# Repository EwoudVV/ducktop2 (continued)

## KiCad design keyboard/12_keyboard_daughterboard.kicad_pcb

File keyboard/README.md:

# keyboard

the RGB map now follows the physical rows. the board is four layers and
0.8 mm thick, with the same 273.5 x 80 mm outline, 65 key positions, diodes
and J320 position. the existing switch, power and I2C routing is retained.
the local joins between each LED's three anodes are retained too. old links
between incompatible LED banks were cleared or trimmed for the new map.

switches, LEDs and the cable connector stay in their original locked positions.
this is still a routing revision, not an order release.

open `12_keyboard_daughterboard.kicad_pro` in this folder. the schematic,
PCB, rules and library tables beside it are the current files.

the layer plan is F.Cu for components and signals, In1.Cu for GND,
In2.Cu for extra signals and local power copper, and B.Cu for signals and
ground fill. a rule blocks non-ground tracks on In1.Cu while allowing
signal vias through it. the current ground zone and stitching are retained.
the dielectric build is provisional; confirm a 0.8 mm four-layer stackup
with the fabricator before ordering.

## LEDs and power

i picked Everlight `19-337/R6GHBHC-C02/2T` LEDs, LCSC `C409504`. each is
1.6 x 1.6 x 0.35 mm and has separate connections for all three colours.
the IS31FL3743A driver, U320, handles all 65 keys over I2C at address
`0x2f`. there is no daisy-chained data connection between the LEDs.

each LED sits 2.8 mm above its switch centre in the top view, inside
CHERRY's auxiliary component area. the maximum LED body height is
0.45 mm; allowing 0.05 mm of solder gives 0.50 mm against CHERRY's
0.8 mm limit. the copper pads fit the allowed area too, with a minimum
nominal edge margin of 0.075 mm. check the first assembled LED and switch
before fitting the rest. the LEDs have to go on before the switches.

R320 is 33.2k, 1%. using the driver's published maximum current at its
stated 3.6 V / 25 C test condition and the resistor's low tolerance gives
11.23 mA per active sink. only 18 sinks run at once, so the total is about
0.202 A before logic and pull-ups. the 5 V feed has a 0.25 A design budget,
below U310's roughly 0.4 A nominal limit and J320's 0.5 A contact rating.
this is a design calculation; measure current and driver temperature at
full white on the first assembled board. the scan duty also means the
average current per colour is about 1 mA at full brightness.

the keyboard gets switched 5 V on J320 pin 29. its 3.3 V buffer supply is
pin 2, through the now-populated R387 on the center board. **keep R386
unpopulated**, since it bypasses the current-limited switch. U321 is a
TCA9517A: its A side faces the main 3.3 V bus and its B side faces the 5 V
RGB driver. this keeps the
unpowered driver isolated. do not swap its sides or put 5 V pull-ups on
the EC side.

## routing order

1. start with U320's exposed ground pad, supply pins and decoupling.
   keep C322/C323 close to VCC, C324/C325 close to PVCC, and C320 beside
   U321's 3.3 V pin. give the exposed pad a short, broad ground connection
   and a return to the In1.Cu ground plane. keep ordinary open vias out of
   the exposed paste area; agree any filled or capped thermal vias with
   the assembler. R320 should have a quiet return to U320's ground.
2. route the 5 V feed and ground returns with at least the selected
   0.5 mm width where space allows. use short neckdowns at fine-pitch pads.
   add the In1.Cu ground plane, ground fill on the outer layers and enough
   stitching to connect the surface pads. preserve the switch keepouts.
3. route the RGB scan banks mainly down the keyboard and the colour sinks
   along the key rows. each bank has one key from every physical row, with
   one extra key on ten banks. use the table below and the [key map](rgb-key-map.csv).
   RGB_SW feeds use 0.4 mm and sinks use 0.2 mm. local anode joins already
   belong to their new bank; do not join neighbouring LEDs just because
   they used to share a bank.
4. finish any remaining keyboard-matrix and I2C connections at 0.2 mm. there is no controlled
   impedance requirement here. keep I2C away from long parallel LED power
   runs, and keep the driver-side pull-ups local. do not add extra EC-side
   pull-ups. the matrix diode direction is already set in the schematic.
5. add ground stitching, refill, and run DRC with schematic parity.
   check the full native unconnected count: the CLI report stops at 499.
   the current saved routing count is recorded in the [checks](../verification/keyboard-rgb.md).

| physical row | red cathode | green cathode | blue cathode |
| --- | --- | --- | --- |
| number row | RGB_RED01 | RGB_CS02 | RGB_CS03 |
| Q row | RGB_RED04 | RGB_CS05 | RGB_CS06 |
| home row | RGB_RED07 | RGB_CS08 | RGB_CS09 |
| shift row | RGB_RED10 | RGB_CS11 | RGB_CS12 |
| bottom row | RGB_RED13 | RGB_CS14 | RGB_CS15 |
| ten extra keys | RGB_RED16 | RGB_CS17 | RGB_CS18 |

55 keys use their physical row's sink group. the ten extra keys use the
last group, so two keys never share the same bank and colour channel.
R330-R335 remain between the driver's red CS outputs and the RGB_RED nets.
the firmware table and CSV use the same assignments as the schematic.

the minimum clearance and track width are 0.15 mm, with 0.5/0.2 mm vias.
these are routing settings, not a factory approval. confirm the final
0.8 mm stackup and manufacturing limits when ordering.

the 65 CHERRY copper-free rectangles are conservatively extended through
**all four layers**. do not put tracks, vias, pads or pours in them.
the custom courtyard rules allow
only each LED to sit under its matching switch. every other courtyard
check stays active. those exceptions depend on the checked LED offset
and body height, so leave the locked LED positions alone.

## firmware and checks

the EC now initialises the driver, loads all channels before enabling
light, and cuts RGB power on an I2C failure or the power-switch fault
signal. the existing host enable command turns on white at 64/255
brightness. per-key RGB and brightness functions are available in the
firmware; a desktop colour picker and animation controls are still to do.
updates happen one bank per main-loop call, so this is a static backlight
driver, not a high-frame-rate effects engine.

the [placement checks](../verification/keyboard-rgb.md) record the current
results. this revision has no fabrication package yet. after routing,
recheck the switch exclusions against the actual exported copper, then
prepare a new BOM, placement file and assembly sequence for the LEDs,
support parts and switches. the old passive-keyboard exporter refuses
this revision until its assembly contract is updated.

part drawings used here: [Everlight LED](https://www.endrich.com/Datenbl%C3%A4tter/Lichtl%C3%B6sungen/Everlight/RGB%20LED/19-337R6GHBHC-C022T.pdf),
[Lumissil driver](https://www.lumissil.com/assets/pdf/core/IS31FL3743A_DS.pdf),
[TI buffer](https://www.ti.com/lit/ds/symlink/tca9517a.pdf), and CHERRY's
VS-10107 revision 03 / PCB-MX-ULP sample drawings.

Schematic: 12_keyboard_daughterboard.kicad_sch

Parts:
C320: 100n 50V buffer 3V3; C_0603_1608Metric; MPN CL10B104KB8NNNC
C321: 10u 25V RGB input bulk; C_0805_2012Metric; MPN CL21A106KAYNNNE
C322: 1u 25V RGB VCC; C_0603_1608Metric; MPN CL10B105KA8NNNC
C323: 100n 50V RGB VCC; C_0603_1608Metric; MPN CL10B104KB8NNNC
C324: 1u 25V RGB PVCC; C_0603_1608Metric; MPN CL10B105KA8NNNC
C325: 100n 50V RGB PVCC / buffer B; C_0603_1608Metric; MPN CL10B104KB8NNNC
C326: 100n 50V RGB startup delay; C_0603_1608Metric; MPN CL10B104KB8NNNC
D320, D321, D322, D323, D324, D325, D326, D327, D328, D329, D330, D331, D332, D333, D334, D335, D336, D337, D338, D339, D340, D341, D342, D343, D344, D345, D346, D347, D348, D349, D350, D351, D352, D353, D354, D355, D356, D357, D358, D359, D360, D361, D362, D363, D364, D365, D366, D367, D368, D369, D370, D371, D372, D373, D374, D375, D376, D377, D378, D379, D380, D381, D382, D383, D384: 1N4148WS; D_SOD-323_JSCJ_1N4148WS; MPN 1N4148WS; LCSC C2128
J320: Keyboard FFC: MX ULP 5x14 matrix on 30-pin EC con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; Hirose_FH12_30_Separate_Mounts; MPN FH12-30S-0.5SH(55); LCSC C506793
LED320: RGB ESC; LED_Everlight_19-337_1616; MPN 19-337/R6GHBHC-C02/2T; LCSC C409504
LED321: RGB 1; LED_Everlight_19-337_1616; MPN 19-337/R6GHBHC-C02/2T; LCSC C409504
LED322: RGB 2; LED_Everlight_19-337_1616; MPN 19-337/R6GHBHC-C02/2T; LCSC C409504
LED323: RGB 3; LED_Everlight_19-337_1616; MPN 19-337/R6GHBHC-C02/2T; LCSC C409504
LED324: RGB 4; LED_Everlight_19-337_1616; MPN 19-337/R6GHBHC-C02/2T; LCSC C409504
LED325: RGB 5; LED_Everlight_19-337_1616; MPN 19-337/R6GHBHC-C02/2T; LCSC C409504
LED326: RGB 6; LED_Everlight_19-337_1616; MPN 19-337/R6GHBHC-C02/2T; LCSC C409504
LED327: RGB 7; LED_Everlight_19-337_1616; MPN 19-337/R6GHBHC-C02/2T; LCSC C409504
LED328: RGB 8; LED_Everlight_19-337_1616; MPN 19-337/R6GHBHC-C02/2T; LCSC C409504
LED329: RGB 9; LED_Everlight_19-337_1616; MPN 19-337/R6GHBHC-C02/2T; LCSC C409504
LED330: RGB 0; LED_Everlight_19-337_1616; MPN 19-337/R6GHBHC-C02/2T; LCSC C409504
LED331: RGB MINUS; LED_Everlight_19-337_1616; MPN 19-337/R6GHBHC-C02/2T; LCSC C409504
LED332: RGB EQUAL; LED_Everlight_19-337_1616; MPN 19-337/R6GHBHC-C02/2T; LCSC C409504
LED333: RGB BKSP; LED_Everlight_19-337_1616; MPN 19-337/R6GHBHC-C02/2T; LCSC C409504
LED334: RGB TAB; LED_Everlight_19-337_1616; MPN 19-337/R6GHBHC-C02/2T; LCSC C409504
LED335: RGB Q; LED_Everlight_19-337_1616; MPN 19-337/R6GHBHC-C02/2T; LCSC C409504
LED336: RGB W; LED_Everlight_19-337_1616; MPN 19-337/R6GHBHC-C02/2T; LCSC C409504
LED337: RGB E; LED_Everlight_19-337_1616; MPN 19-337/R6GHBHC-C02/2T; LCSC C409504
LED338: RGB R; LED_Everlight_19-337_1616; MPN 19-337/R6GHBHC-C02/2T; LCSC C409504
LED339: RGB T; LED_Everlight_19-337_1616; MPN 19-337/R6GHBHC-C02/2T; LCSC C409504
LED340: RGB Y; LED_Everlight_19-337_1616; MPN 19-337/R6GHBHC-C02/2T; LCSC C409504
LED341: RGB U; LED_Everlight_19-337_1616; MPN 19-337/R6GHBHC-C02/2T; LCSC C409504
LED342: RGB I; LED_Everlight_19-337_1616; MPN 19-337/R6GHBHC-C02/2T; LCSC C409504
LED343: RGB O; LED_Everlight_19-337_1616; MPN 19-337/R6GHBHC-C02/2T; LCSC C409504
LED344: RGB P; LED_Everlight_19-337_1616; MPN 19-337/R6GHBHC-C02/2T; LCSC C409504
LED345: RGB LBRACKET; LED_Everlight_19-337_1616; MPN 19-337/R6GHBHC-C02/2T; LCSC C409504
LED346: RGB RBRACKET; LED_Everlight_19-337_1616; MPN 19-337/R6GHBHC-C02/2T; LCSC C409504
LED347: RGB BSLASH; LED_Everlight_19-337_1616; MPN 19-337/R6GHBHC-C02/2T; LCSC C409504
LED348: RGB CAPS; LED_Everlight_19-337_1616; MPN 19-337/R6GHBHC-C02/2T; LCSC C409504
LED349: RGB A; LED_Everlight_19-337_1616; MPN 19-337/R6GHBHC-C02/2T; LCSC C409504
LED350: RGB S; LED_Everlight_19-337_1616; MPN 19-337/R6GHBHC-C02/2T; LCSC C409504
LED351: RGB D; LED_Everlight_19-337_1616; MPN 19-337/R6GHBHC-C02/2T; LCSC C409504
LED352: RGB F; LED_Everlight_19-337_1616; MPN 19-337/R6GHBHC-C02/2T; LCSC C409504
LED353: RGB G; LED_Everlight_19-337_1616; MPN 19-337/R6GHBHC-C02/2T; LCSC C409504
LED354: RGB H; LED_Everlight_19-337_1616; MPN 19-337/R6GHBHC-C02/2T; LCSC C409504
LED355: RGB J; LED_Everlight_19-337_1616; MPN 19-337/R6GHBHC-C02/2T; LCSC C409504
LED356: RGB K; LED_Everlight_19-337_1616; MPN 19-337/R6GHBHC-C02/2T; LCSC C409504
LED357: RGB L; LED_Everlight_19-337_1616; MPN 19-337/R6GHBHC-C02/2T; LCSC C409504
LED358: RGB SEMICOLON; LED_Everlight_19-337_1616; MPN 19-337/R6GHBHC-C02/2T; LCSC C409504
LED359: RGB QUOTE; LED_Everlight_19-337_1616; MPN 19-337/R6GHBHC-C02/2T; LCSC C409504
LED360: RGB ENTER; LED_Everlight_19-337_1616; MPN 19-337/R6GHBHC-C02/2T; LCSC C409504
LED361: RGB LSHIFT; LED_Everlight_19-337_1616; MPN 19-337/R6GHBHC-C02/2T; LCSC C409504
LED362: RGB Z; LED_Everlight_19-337_1616; MPN 19-337/R6GHBHC-C02/2T; LCSC C409504
LED363: RGB X; LED_Everlight_19-337_1616; MPN 19-337/R6GHBHC-C02/2T; LCSC C409504
LED364: RGB C; LED_Everlight_19-337_1616; MPN 19-337/R6GHBHC-C02/2T; LCSC C409504
LED365: RGB V; LED_Everlight_19-337_1616; MPN 19-337/R6GHBHC-C02/2T; LCSC C409504
LED366: RGB B; LED_Everlight_19-337_1616; MPN 19-337/R6GHBHC-C02/2T; LCSC C409504
LED367: RGB N; LED_Everlight_19-337_1616; MPN 19-337/R6GHBHC-C02/2T; LCSC C409504
LED368: RGB M; LED_Everlight_19-337_1616; MPN 19-337/R6GHBHC-C02/2T; LCSC C409504
LED369: RGB COMMA; LED_Everlight_19-337_1616; MPN 19-337/R6GHBHC-C02/2T; LCSC C409504
LED370: RGB PERIOD; LED_Everlight_19-337_1616; MPN 19-337/R6GHBHC-C02/2T; LCSC C409504
LED371: RGB SLASH; LED_Everlight_19-337_1616; MPN 19-337/R6GHBHC-C02/2T; LCSC C409504
LED372: RGB UP; LED_Everlight_19-337_1616; MPN 19-337/R6GHBHC-C02/2T; LCSC C409504
LED373: RGB RSHIFT; LED_Everlight_19-337_1616; MPN 19-337/R6GHBHC-C02/2T; LCSC C409504
LED374: RGB CTRL; LED_Everlight_19-337_1616; MPN 19-337/R6GHBHC-C02/2T; LCSC C409504
LED375: RGB FN; LED_Everlight_19-337_1616; MPN 19-337/R6GHBHC-C02/2T; LCSC C409504
LED376: RGB SUPER; LED_Everlight_19-337_1616; MPN 19-337/R6GHBHC-C02/2T; LCSC C409504
LED377: RGB LALT; LED_Everlight_19-337_1616; MPN 19-337/R6GHBHC-C02/2T; LCSC C409504
LED378: RGB SPACE_L; LED_Everlight_19-337_1616; MPN 19-337/R6GHBHC-C02/2T; LCSC C409504
LED379: RGB SPACE_R; LED_Everlight_19-337_1616; MPN 19-337/R6GHBHC-C02/2T; LCSC C409504
LED380: RGB RALT; LED_Everlight_19-337_1616; MPN 19-337/R6GHBHC-C02/2T; LCSC C409504
LED381: RGB MENU; LED_Everlight_19-337_1616; MPN 19-337/R6GHBHC-C02/2T; LCSC C409504
LED382: RGB LEFT; LED_Everlight_19-337_1616; MPN 19-337/R6GHBHC-C02/2T; LCSC C409504
LED383: RGB DOWN; LED_Everlight_19-337_1616; MPN 19-337/R6GHBHC-C02/2T; LCSC C409504
LED384: RGB RIGHT; LED_Everlight_19-337_1616; MPN 19-337/R6GHBHC-C02/2T; LCSC C409504
R320: 33.2k 1% RGB current limit; R_0603_1608Metric; MPN RC0603FR-0733K2L
R321: 2.2k RGB SCL pull-up; R_0603_1608Metric; MPN RC0603FR-072K2L
R322: 2.2k RGB SDA pull-up; R_0603_1608Metric; MPN RC0603FR-072K2L
R323: 100k RGB startup pull-up; R_0603_1608Metric; MPN RC0603FR-07100KL
R330, R331, R332, R333, R334, R335: 100R red-channel heat sharing; R_0603_1608Metric; MPN RC0603FR-07100RL
SW320: Esc 1u; Cherry_MX_ULP_SMD; MPN MX6C-T3NB
SW321: 1 1u; Cherry_MX_ULP_SMD; MPN MX6C-T3NB
SW322: 2 1u; Cherry_MX_ULP_SMD; MPN MX6C-T3NB
SW323: 3 1u; Cherry_MX_ULP_SMD; MPN MX6C-T3NB
SW324: 4 1u; Cherry_MX_ULP_SMD; MPN MX6C-T3NB
SW325: 5 1u; Cherry_MX_ULP_SMD; MPN MX6C-T3NB
SW326: 6 1u; Cherry_MX_ULP_SMD; MPN MX6C-T3NB
SW327: 7 1u; Cherry_MX_ULP_SMD; MPN MX6C-T3NB
SW328: 8 1u; Cherry_MX_ULP_SMD; MPN MX6C-T3NB
SW329: 9 1u; Cherry_MX_ULP_SMD; MPN MX6C-T3NB
SW330: 0 1u; Cherry_MX_ULP_SMD; MPN MX6C-T3NB
SW331: Minus 1u; Cherry_MX_ULP_SMD; MPN MX6C-T3NB
SW332: Equal 1u; Cherry_MX_ULP_SMD; MPN MX6C-T3NB
SW333: Backspace 1.75u; Cherry_MX_ULP_SMD; MPN MX6C-T3NB
SW334: Tab 1.25u; Cherry_MX_ULP_SMD; MPN MX6C-T3NB
SW335: Q 1u; Cherry_MX_ULP_SMD; MPN MX6C-T3NB
SW336: W 1u; Cherry_MX_ULP_SMD; MPN MX6C-T3NB
SW337: E 1u; Cherry_MX_ULP_SMD; MPN MX6C-T3NB
SW338: R 1u; Cherry_MX_ULP_SMD; MPN MX6C-T3NB
SW339: T 1u; Cherry_MX_ULP_SMD; MPN MX6C-T3NB
SW340: Y 1u; Cherry_MX_ULP_SMD; MPN MX6C-T3NB
SW341: U 1u; Cherry_MX_ULP_SMD; MPN MX6C-T3NB
SW342: I 1u; Cherry_MX_ULP_SMD; MPN MX6C-T3NB
SW343: O 1u; Cherry_MX_ULP_SMD; MPN MX6C-T3NB
SW344: P 1u; Cherry_MX_ULP_SMD; MPN MX6C-T3NB
SW345: [ 1u; Cherry_MX_ULP_SMD; MPN MX6C-T3NB
SW346: ] 1u; Cherry_MX_ULP_SMD; MPN MX6C-T3NB
SW347: Backslash 1u; Cherry_MX_ULP_SMD; MPN MX6C-T3NB
SW348: Caps 1.5u; Cherry_MX_ULP_SMD; MPN MX6C-T3NB
SW349: A 1u; Cherry_MX_ULP_SMD; MPN MX6C-T3NB
SW350: S 1u; Cherry_MX_ULP_SMD; MPN MX6C-T3NB
SW351: D 1u; Cherry_MX_ULP_SMD; MPN MX6C-T3NB
SW352: F 1u; Cherry_MX_ULP_SMD; MPN MX6C-T3NB
SW353: G 1u; Cherry_MX_ULP_SMD; MPN MX6C-T3NB
SW354: H 1u; Cherry_MX_ULP_SMD; MPN MX6C-T3NB
SW355: J 1u; Cherry_MX_ULP_SMD; MPN MX6C-T3NB
SW356: K 1u; Cherry_MX_ULP_SMD; MPN MX6C-T3NB
SW357: L 1u; Cherry_MX_ULP_SMD; MPN MX6C-T3NB
SW358: Semicolon 1u; Cherry_MX_ULP_SMD; MPN MX6C-T3NB
SW359: Quote 1u; Cherry_MX_ULP_SMD; MPN MX6C-T3NB
SW360: Enter 1.75u; Cherry_MX_ULP_SMD; MPN MX6C-T3NB
SW361: Shift L 1.75u; Cherry_MX_ULP_SMD; MPN MX6C-T3NB
SW362: Z 1u; Cherry_MX_ULP_SMD; MPN MX6C-T3NB
SW363: X 1u; Cherry_MX_ULP_SMD; MPN MX6C-T3NB
SW364: C 1u; Cherry_MX_ULP_SMD; MPN MX6C-T3NB
SW365: V 1u; Cherry_MX_ULP_SMD; MPN MX6C-T3NB
SW366: B 1u; Cherry_MX_ULP_SMD; MPN MX6C-T3NB
SW367: N 1u; Cherry_MX_ULP_SMD; MPN MX6C-T3NB
SW368: M 1u; Cherry_MX_ULP_SMD; MPN MX6C-T3NB
SW369: Comma 1u; Cherry_MX_ULP_SMD; MPN MX6C-T3NB
SW370: Period 1u; Cherry_MX_ULP_SMD; MPN MX6C-T3NB
SW371: Slash 1u; Cherry_MX_ULP_SMD; MPN MX6C-T3NB
SW372: Up 1u; Cherry_MX_ULP_SMD; MPN MX6C-T3NB
SW373: Shift R 1.25u; Cherry_MX_ULP_SMD; MPN MX6C-T3NB
SW374: Ctrl 1u; Cherry_MX_ULP_SMD; MPN MX6C-T3NB
SW375: Fn 1u; Cherry_MX_ULP_SMD; MPN MX6C-T3NB
SW376: Super 1u; Cherry_MX_ULP_SMD; MPN MX6C-T3NB
SW377: Alt L 1u; Cherry_MX_ULP_SMD; MPN MX6C-T3NB
SW378: Space L 2.25u; Cherry_MX_ULP_SMD; MPN MX6C-T3NB
SW379: Space R 2.25u; Cherry_MX_ULP_SMD; MPN MX6C-T3NB
SW380: Alt R 1u; Cherry_MX_ULP_SMD; MPN MX6C-T3NB
SW381: Menu 1u; Cherry_MX_ULP_SMD; MPN MX6C-T3NB
SW382: Left 1u; Cherry_MX_ULP_SMD; MPN MX6C-T3NB
SW383: Down 1u; Cherry_MX_ULP_SMD; MPN MX6C-T3NB
SW384: Right 1u; Cherry_MX_ULP_SMD; MPN MX6C-T3NB
TPK1: KB_RGB_5V; TestPoint_Pad_D1.0mm
TPK2: GND; TestPoint_Pad_D1.0mm
TPK3: MCU_3V3; TestPoint_Pad_D1.0mm
TPK4: RGB_SCL; TestPoint_Pad_D1.0mm
TPK5: RGB_SDA; TestPoint_Pad_D1.0mm
TPK6: RGB_SDB; TestPoint_Pad_D1.0mm
U320: IS31FL3743A-QULS4-TR; IS31FL3743A_UQFN40; MPN IS31FL3743A-QULS4-TR; LCSC C2678953
U321: TCA9517ADGKR; VSSOP-8_3x3mm_P0.65mm; MPN TCA9517ADGKR; LCSC C201698

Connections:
GND: C320.2, C321.2, C322.2, C323.2, C324.2, C325.2, C326.2, J320.1, J320.30, R320.2, SW320.MP (FRAME), SW321.MP (FRAME), SW322.MP (FRAME), SW323.MP (FRAME), SW324.MP (FRAME), SW325.MP (FRAME), SW326.MP (FRAME), SW327.MP (FRAME), SW328.MP (FRAME), SW329.MP (FRAME), SW330.MP (FRAME), SW331.MP (FRAME), SW332.MP (FRAME), SW333.MP (FRAME), SW334.MP (FRAME), SW335.MP (FRAME), SW336.MP (FRAME), SW337.MP (FRAME), SW338.MP (FRAME), SW339.MP (FRAME), SW340.MP (FRAME), SW341.MP (FRAME), SW342.MP (FRAME), SW343.MP (FRAME), SW344.MP (FRAME), SW345.MP (FRAME), SW346.MP (FRAME), SW347.MP (FRAME), SW348.MP (FRAME), SW349.MP (FRAME), SW350.MP (FRAME), SW351.MP (FRAME), SW352.MP (FRAME), SW353.MP (FRAME), SW354.MP (FRAME), SW355.MP (FRAME), SW356.MP (FRAME), SW357.MP (FRAME), SW358.MP (FRAME), SW359.MP (FRAME), SW360.MP (FRAME), SW361.MP (FRAME), SW362.MP (FRAME), SW363.MP (FRAME), SW364.MP (FRAME), SW365.MP (FRAME), SW366.MP (FRAME), SW367.MP (FRAME), SW368.MP (FRAME), SW369.MP (FRAME), SW370.MP (FRAME), SW371.MP (FRAME), SW372.MP (FRAME), SW373.MP (FRAME), SW374.MP (FRAME), SW375.MP (FRAME), SW376.MP (FRAME), SW377.MP (FRAME), SW378.MP (FRAME), SW379.MP (FRAME), SW380.MP (FRAME), SW381.MP (FRAME), SW382.MP (FRAME), SW383.MP (FRAME), SW384.MP (FRAME), TPK2.1, U320.16 (PGND), U320.23 (GND), U320.41 (EP), U321.4 (GND)
I2C_SCL: J320.3, U321.2 (SCLA)
I2C_SDA: J320.4, U321.3 (SDAA)
KB_COL0: J320.13, SW320.2 (B), SW334.2 (B), SW348.2 (B), SW361.2 (B), SW374.2 (B)
KB_COL1: J320.14, SW321.2 (B), SW335.2 (B), SW349.2 (B), SW362.2 (B), SW375.2 (B)
KB_COL2: J320.15, SW322.2 (B), SW336.2 (B), SW350.2 (B), SW363.2 (B), SW376.2 (B)
KB_COL3: J320.16, SW323.2 (B), SW337.2 (B), SW351.2 (B), SW364.2 (B), SW377.2 (B)
KB_COL4: J320.17, SW324.2 (B), SW338.2 (B), SW352.2 (B), SW365.2 (B), SW378.2 (B)
KB_COL5: J320.18, SW325.2 (B), SW339.2 (B), SW353.2 (B), SW366.2 (B), SW379.2 (B)
KB_COL6: J320.19, SW326.2 (B), SW340.2 (B), SW354.2 (B), SW367.2 (B), SW380.2 (B)
KB_COL7: J320.20, SW327.2 (B), SW341.2 (B), SW355.2 (B), SW368.2 (B), SW381.2 (B)
KB_COL8: J320.21, SW328.2 (B), SW342.2 (B), SW356.2 (B), SW369.2 (B)
KB_COL9: J320.22, SW329.2 (B), SW343.2 (B), SW357.2 (B), SW370.2 (B), SW382.2 (B)
KB_COL10: J320.23, SW330.2 (B), SW344.2 (B), SW358.2 (B), SW371.2 (B), SW383.2 (B)
KB_COL11: J320.24, SW331.2 (B), SW345.2 (B), SW359.2 (B), SW372.2 (B), SW384.2 (B)
KB_COL12: J320.25, SW332.2 (B), SW346.2 (B), SW360.2 (B), SW373.2 (B)
KB_COL13: J320.26, SW333.2 (B), SW347.2 (B)
KB_R0_C0_ESC: D320.1 (K), SW320.1 (A)
KB_R0_C1_1: D321.1 (K), SW321.1 (A)
KB_R0_C2_2: D322.1 (K), SW322.1 (A)
KB_R0_C3_3: D323.1 (K), SW323.1 (A)
KB_R0_C4_4: D324.1 (K), SW324.1 (A)
KB_R0_C5_5: D325.1 (K), SW325.1 (A)
KB_R0_C6_6: D326.1 (K), SW326.1 (A)
KB_R0_C7_7: D327.1 (K), SW327.1 (A)
KB_R0_C8_8: D328.1 (K), SW328.1 (A)
KB_R0_C9_9: D329.1 (K), SW329.1 (A)
KB_R0_C10_0: D330.1 (K), SW330.1 (A)
KB_R0_C11_MINUS: D331.1 (K), SW331.1 (A)
KB_R0_C12_EQUAL: D332.1 (K), SW332.1 (A)
KB_R0_C13_BKSP: D333.1 (K), SW333.1 (A)
KB_R1_C0_TAB: D334.1 (K), SW334.1 (A)
KB_R1_C1_Q: D335.1 (K), SW335.1 (A)
KB_R1_C2_W: D336.1 (K), SW336.1 (A)
KB_R1_C3_E: D337.1 (K), SW337.1 (A)
KB_R1_C4_R: D338.1 (K), SW338.1 (A)
KB_R1_C5_T: D339.1 (K), SW339.1 (A)
KB_R1_C6_Y: D340.1 (K), SW340.1 (A)
KB_R1_C7_U: D341.1 (K), SW341.1 (A)
KB_R1_C8_I: D342.1 (K), SW342.1 (A)
KB_R1_C9_O: D343.1 (K), SW343.1 (A)
KB_R1_C10_P: D344.1 (K), SW344.1 (A)
KB_R1_C11_LBRACKET: D345.1 (K), SW345.1 (A)
KB_R1_C12_RBRACKET: D346.1 (K), SW346.1 (A)
KB_R1_C13_BSLASH: D347.1 (K), SW347.1 (A)
KB_R2_C0_CAPS: D348.1 (K), SW348.1 (A)
KB_R2_C1_A: D349.1 (K), SW349.1 (A)
KB_R2_C2_S: D350.1 (K), SW350.1 (A)
KB_R2_C3_D: D351.1 (K), SW351.1 (A)
KB_R2_C4_F: D352.1 (K), SW352.1 (A)
KB_R2_C5_G: D353.1 (K), SW353.1 (A)
KB_R2_C6_H: D354.1 (K), SW354.1 (A)
KB_R2_C7_J: D355.1 (K), SW355.1 (A)
KB_R2_C8_K: D356.1 (K), SW356.1 (A)
KB_R2_C9_L: D357.1 (K), SW357.1 (A)
KB_R2_C10_SEMICOLON: D358.1 (K), SW358.1 (A)
KB_R2_C11_QUOTE: D359.1 (K), SW359.1 (A)
KB_R2_C12_ENTER: D360.1 (K), SW360.1 (A)
KB_R3_C0_LSHIFT: D361.1 (K), SW361.1 (A)
KB_R3_C1_Z: D362.1 (K), SW362.1 (A)
KB_R3_C2_X: D363.1 (K), SW363.1 (A)
KB_R3_C3_C: D364.1 (K), SW364.1 (A)
KB_R3_C4_V: D365.1 (K), SW365.1 (A)
KB_R3_C5_B: D366.1 (K), SW366.1 (A)
KB_R3_C6_N: D367.1 (K), SW367.1 (A)
KB_R3_C7_M: D368.1 (K), SW368.1 (A)
KB_R3_C8_COMMA: D369.1 (K), SW369.1 (A)
KB_R3_C9_PERIOD: D370.1 (K), SW370.1 (A)
KB_R3_C10_SLASH: D371.1 (K), SW371.1 (A)
KB_R3_C11_UP: D372.1 (K), SW372.1 (A)
KB_R3_C12_RSHIFT: D373.1 (K), SW373.1 (A)
KB_R4_C0_CTRL: D374.1 (K), SW374.1 (A)
KB_R4_C1_FN: D375.1 (K), SW375.1 (A)
KB_R4_C2_SUPER: D376.1 (K), SW376.1 (A)
KB_R4_C3_LALT: D377.1 (K), SW377.1 (A)
KB_R4_C4_SPACE_L: D378.1 (K), SW378.1 (A)
KB_R4_C5_SPACE_R: D379.1 (K), SW379.1 (A)
KB_R4_C6_RALT: D380.1 (K), SW380.1 (A)
KB_R4_C7_MENU: D381.1 (K), SW381.1 (A)
KB_R4_C9_LEFT: D382.1 (K), SW382.1 (A)
KB_R4_C10_DOWN: D383.1 (K), SW383.1 (A)
KB_R4_C11_RIGHT: D384.1 (K), SW384.1 (A)
KB_RGB_5V: C321.1, C322.1, C323.1, C324.1, C325.1, J320.29, R321.1, R322.1, R323.1, TPK1.1, U320.5 (PVCC), U320.22 (VCC), U320.24 (ADDR2), U320.25 (ADDR1), U321.8 (VCCB)
KB_ROW0: D320.2 (A), D321.2 (A), D322.2 (A), D323.2 (A), D324.2 (A), D325.2 (A), D326.2 (A), D327.2 (A), D328.2 (A), D329.2 (A), D330.2 (A), D331.2 (A), D332.2 (A), D333.2 (A), J320.5
KB_ROW1: D334.2 (A), D335.2 (A), D336.2 (A), D337.2 (A), D338.2 (A), D339.2 (A), D340.2 (A), D341.2 (A), D342.2 (A), D343.2 (A), D344.2 (A), D345.2 (A), D346.2 (A), D347.2 (A), J320.6
KB_ROW2: D348.2 (A), D349.2 (A), D350.2 (A), D351.2 (A), D352.2 (A), D353.2 (A), D354.2 (A), D355.2 (A), D356.2 (A), D357.2 (A), D358.2 (A), D359.2 (A), D360.2 (A), J320.7
KB_ROW3: D361.2 (A), D362.2 (A), D363.2 (A), D364.2 (A), D365.2 (A), D366.2 (A), D367.2 (A), D368.2 (A), D369.2 (A), D370.2 (A), D371.2 (A), D372.2 (A), D373.2 (A), J320.8
KB_ROW4: D374.2 (A), D375.2 (A), D376.2 (A), D377.2 (A), D378.2 (A), D379.2 (A), D380.2 (A), D381.2 (A), D382.2 (A), D383.2 (A), D384.2 (A), J320.9
MCU_3V3: C320.1, J320.2, TPK3.1, U321.1 (VCCA), U321.5 (EN)
RGB_CS01: R330.1, U320.39 (CS01)
RGB_CS02: LED320.6 (G_K), LED322.6 (G_K), LED323.6 (G_K), LED324.6 (G_K), LED325.6 (G_K), LED327.6 (G_K), LED328.6 (G_K), LED329.6 (G_K), LED331.6 (G_K), LED332.6 (G_K), LED333.6 (G_K), U320.38 (CS02)
RGB_CS03: LED320.2 (B_K), LED322.2 (B_K), LED323.2 (B_K), LED324.2 (B_K), LED325.2 (B_K), LED327.2 (B_K), LED328.2 (B_K), LED329.2 (B_K), LED331.2 (B_K), LED332.2 (B_K), LED333.2 (B_K), U320.37 (CS03)
RGB_CS04: R331.1, U320.36 (CS04)
RGB_CS05: LED334.6 (G_K), LED335.6 (G_K), LED336.6 (G_K), LED338.6 (G_K), LED339.6 (G_K), LED340.6 (G_K), LED342.6 (G_K), LED343.6 (G_K), LED344.6 (G_K), LED345.6 (G_K), LED347.6 (G_K), U320.35 (CS05)
RGB_CS06: LED334.2 (B_K), LED335.2 (B_K), LED336.2 (B_K), LED338.2 (B_K), LED339.2 (B_K), LED340.2 (B_K), LED342.2 (B_K), LED343.2 (B_K), LED344.2 (B_K), LED345.2 (B_K), LED347.2 (B_K), U320.34 (CS06)
RGB_CS07: R332.1, U320.33 (CS07)
RGB_CS08: LED348.6 (G_K), LED349.6 (G_K), LED350.6 (G_K), LED351.6 (G_K), LED353.6 (G_K), LED354.6 (G_K), LED355.6 (G_K), LED357.6 (G_K), LED358.6 (G_K), LED359.6 (G_K), LED360.6 (G_K), U320.32 (CS08)
RGB_CS09: LED348.2 (B_K), LED349.2 (B_K), LED350.2 (B_K), LED351.2 (B_K), LED353.2 (B_K), LED354.2 (B_K), LED355.2 (B_K), LED357.2 (B_K), LED358.2 (B_K), LED359.2 (B_K), LED360.2 (B_K), U320.31 (CS09)
RGB_CS10: R333.1, U320.21 (CS10)
RGB_CS11: LED361.6 (G_K), LED362.6 (G_K), LED363.6 (G_K), LED364.6 (G_K), LED365.6 (G_K), LED367.6 (G_K), LED368.6 (G_K), LED369.6 (G_K), LED370.6 (G_K), LED372.6 (G_K), LED373.6 (G_K), U320.20 (CS11)
RGB_CS12: LED361.2 (B_K), LED362.2 (B_K), LED363.2 (B_K), LED364.2 (B_K), LED365.2 (B_K), LED367.2 (B_K), LED368.2 (B_K), LED369.2 (B_K), LED370.2 (B_K), LED372.2 (B_K), LED373.2 (B_K), U320.19 (CS12)
RGB_CS13: R334.1, U320.18 (CS13)
RGB_CS14: LED374.6 (G_K), LED375.6 (G_K), LED376.6 (G_K), LED377.6 (G_K), LED378.6 (G_K), LED379.6 (G_K), LED380.6 (G_K), LED381.6 (G_K), LED382.6 (G_K), LED383.6 (G_K), LED384.6 (G_K), U320.17 (CS14)
RGB_CS15: LED374.2 (B_K), LED375.2 (B_K), LED376.2 (B_K), LED377.2 (B_K), LED378.2 (B_K), LED379.2 (B_K), LED380.2 (B_K), LED381.2 (B_K), LED382.2 (B_K), LED383.2 (B_K), LED384.2 (B_K), U320.15 (CS15)
RGB_CS16: R335.1, U320.14 (CS16)
RGB_CS17: LED321.6 (G_K), LED326.6 (G_K), LED330.6 (G_K), LED337.6 (G_K), LED341.6 (G_K), LED346.6 (G_K), LED352.6 (G_K), LED356.6 (G_K), LED366.6 (G_K), LED371.6 (G_K), U320.13 (CS17)
RGB_CS18: LED321.2 (B_K), LED326.2 (B_K), LED330.2 (B_K), LED337.2 (B_K), LED341.2 (B_K), LED346.2 (B_K), LED352.2 (B_K), LED356.2 (B_K), LED366.2 (B_K), LED371.2 (B_K), U320.12 (CS18)
RGB_ISET: R320.1, U320.29 (ISET)
RGB_RED01: LED320.4 (R_K), LED322.4 (R_K), LED323.4 (R_K), LED324.4 (R_K), LED325.4 (R_K), LED327.4 (R_K), LED328.4 (R_K), LED329.4 (R_K), LED331.4 (R_K), LED332.4 (R_K), LED333.4 (R_K), R330.2
RGB_RED04: LED334.4 (R_K), LED335.4 (R_K), LED336.4 (R_K), LED338.4 (R_K), LED339.4 (R_K), LED340.4 (R_K), LED342.4 (R_K), LED343.4 (R_K), LED344.4 (R_K), LED345.4 (R_K), LED347.4 (R_K), R331.2
RGB_RED07: LED348.4 (R_K), LED349.4 (R_K), LED350.4 (R_K), LED351.4 (R_K), LED353.4 (R_K), LED354.4 (R_K), LED355.4 (R_K), LED357.4 (R_K), LED358.4 (R_K), LED359.4 (R_K), LED360.4 (R_K), R332.2
RGB_RED10: LED361.4 (R_K), LED362.4 (R_K), LED363.4 (R_K), LED364.4 (R_K), LED365.4 (R_K), LED367.4 (R_K), LED368.4 (R_K), LED369.4 (R_K), LED370.4 (R_K), LED372.4 (R_K), LED373.4 (R_K), R333.2
RGB_RED13: LED374.4 (R_K), LED375.4 (R_K), LED376.4 (R_K), LED377.4 (R_K), LED378.4 (R_K), LED379.4 (R_K), LED380.4 (R_K), LED381.4 (R_K), LED382.4 (R_K), LED383.4 (R_K), LED384.4 (R_K), R334.2
RGB_RED16: LED321.4 (R_K), LED326.4 (R_K), LED330.4 (R_K), LED337.4 (R_K), LED341.4 (R_K), LED346.4 (R_K), LED352.4 (R_K), LED356.4 (R_K), LED366.4 (R_K), LED371.4 (R_K), R335.2
RGB_SCL: R321.2, TPK4.1, U320.27 (SCL), U321.7 (SCLB)
RGB_SDA: R322.2, TPK5.1, U320.28 (SDA), U321.6 (SDAB)
RGB_SDB: C326.1, R323.2, TPK6.1, U320.26 (SDB)
RGB_SW01: LED321.1 (B_A), LED321.3 (R_A), LED321.5 (G_A), LED322.1 (B_A), LED322.3 (R_A), LED322.5 (G_A), LED335.1 (B_A), LED335.3 (R_A), LED335.5 (G_A), LED349.1 (B_A), LED349.3 (R_A), LED349.5 (G_A), LED362.1 (B_A), LED362.3 (R_A), LED362.5 (G_A), LED375.1 (B_A), LED375.3 (R_A), LED375.5 (G_A), U320.6 (SW01)
RGB_SW02: LED323.1 (B_A), LED323.3 (R_A), LED323.5 (G_A), LED336.1 (B_A), LED336.3 (R_A), LED336.5 (G_A), LED337.1 (B_A), LED337.3 (R_A), LED337.5 (G_A), LED350.1 (B_A), LED350.3 (R_A), LED350.5 (G_A), LED363.1 (B_A), LED363.3 (R_A), LED363.5 (G_A), LED376.1 (B_A), LED376.3 (R_A), LED376.5 (G_A), U320.4 (SW02)
RGB_SW03: LED324.1 (B_A), LED324.3 (R_A), LED324.5 (G_A), LED338.1 (B_A), LED338.3 (R_A), LED338.5 (G_A), LED351.1 (B_A), LED351.3 (R_A), LED351.5 (G_A), LED352.1 (B_A), LED352.3 (R_A), LED352.5 (G_A), LED364.1 (B_A), LED364.3 (R_A), LED364.5 (G_A), LED377.1 (B_A), LED377.3 (R_A), LED377.5 (G_A), U320.7 (SW03)
RGB_SW04: LED325.1 (B_A), LED325.3 (R_A), LED325.5 (G_A), LED326.1 (B_A), LED326.3 (R_A), LED326.5 (G_A), LED339.1 (B_A), LED339.3 (R_A), LED339.5 (G_A), LED353.1 (B_A), LED353.3 (R_A), LED353.5 (G_A), LED365.1 (B_A), LED365.3 (R_A), LED365.5 (G_A), LED378.1 (B_A), LED378.3 (R_A), LED378.5 (G_A), U320.3 (SW04)
RGB_SW05: LED327.1 (B_A), LED327.3 (R_A), LED327.5 (G_A), LED340.1 (B_A), LED340.3 (R_A), LED340.5 (G_A), LED354.1 (B_A), LED354.3 (R_A), LED354.5 (G_A), LED366.1 (B_A), LED366.3 (R_A), LED366.5 (G_A), LED367.1 (B_A), LED367.3 (R_A), LED367.5 (G_A), LED379.1 (B_A), LED379.3 (R_A), LED379.5 (G_A), U320.8 (SW05)
RGB_SW06: LED328.1 (B_A), LED328.3 (R_A), LED328.5 (G_A), LED341.1 (B_A), LED341.3 (R_A), LED341.5 (G_A), LED342.1 (B_A), LED342.3 (R_A), LED342.5 (G_A), LED355.1 (B_A), LED355.3 (R_A), LED355.5 (G_A), LED368.1 (B_A), LED368.3 (R_A), LED368.5 (G_A), LED380.1 (B_A), LED380.3 (R_A), LED380.5 (G_A), U320.2 (SW06)
RGB_SW07: LED329.1 (B_A), LED329.3 (R_A), LED329.5 (G_A), LED343.1 (B_A), LED343.3 (R_A), LED343.5 (G_A), LED356.1 (B_A), LED356.3 (R_A), LED356.5 (G_A), LED357.1 (B_A), LED357.3 (R_A), LED357.5 (G_A), LED369.1 (B_A), LED369.3 (R_A), LED369.5 (G_A), LED381.1 (B_A), LED381.3 (R_A), LED381.5 (G_A), U320.9 (SW07)
RGB_SW08: LED330.1 (B_A), LED330.3 (R_A), LED330.5 (G_A), LED331.1 (B_A), LED331.3 (R_A), LED331.5 (G_A), LED344.1 (B_A), LED344.3 (R_A), LED344.5 (G_A), LED358.1 (B_A), LED358.3 (R_A), LED358.5 (G_A), LED370.1 (B_A), LED370.3 (R_A), LED370.5 (G_A), LED382.1 (B_A), LED382.3 (R_A), LED382.5 (G_A), U320.1 (SW08)
RGB_SW09: LED332.1 (B_A), LED332.3 (R_A), LED332.5 (G_A), LED345.1 (B_A), LED345.3 (R_A), LED345.5 (G_A), LED359.1 (B_A), LED359.3 (R_A), LED359.5 (G_A), LED371.1 (B_A), LED371.3 (R_A), LED371.5 (G_A), LED372.1 (B_A), LED372.3 (R_A), LED372.5 (G_A), LED383.1 (B_A), LED383.3 (R_A), LED383.5 (G_A), U320.10 (SW09)
RGB_SW10: LED333.1 (B_A), LED333.3 (R_A), LED333.5 (G_A), LED346.1 (B_A), LED346.3 (R_A), LED346.5 (G_A), LED347.1 (B_A), LED347.3 (R_A), LED347.5 (G_A), LED360.1 (B_A), LED360.3 (R_A), LED360.5 (G_A), LED373.1 (B_A), LED373.3 (R_A), LED373.5 (G_A), LED384.1 (B_A), LED384.3 (R_A), LED384.5 (G_A), U320.40 (SW10)
RGB_SW11: LED320.1 (B_A), LED320.3 (R_A), LED320.5 (G_A), LED334.1 (B_A), LED334.3 (R_A), LED334.5 (G_A), LED348.1 (B_A), LED348.3 (R_A), LED348.5 (G_A), LED361.1 (B_A), LED361.3 (R_A), LED361.5 (G_A), LED374.1 (B_A), LED374.3 (R_A), LED374.5 (G_A), U320.11 (SW11)

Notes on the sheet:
== Ducktop2 MX ULP keyboard daughterboard ==
65-key compact laptop-style layout, Cherry MX Ultra Low Profile tactile switches, one diode per key.
RGB revision: same 273.5 x 80.0 mm outline, key positions and active matrix contacts.
This sheet is the keyboard PCB itself: switches, matrix diodes, EC FFC, and bring-up notes.
== 5x14 switch matrix, diode direction locked for EC firmware ==
Scan assumption: EC drives one column low at a time and reads rows with pull-ups. Each key path is ROW -> diode anode -> diode cathode -> switch -> COL.
== J320 keyboard FFC / board-to-board connector ==
NOTES:
Use CHERRY MX6C-T3NB tactile switches. The five MP fixation lands connect to GND per CHERRY PCB-reference-design; pins 1/2 form the matrix.
D320-D384 are JSCJ 1N4148WS, SOD-323, C2128. Pin 2 is anode on KB_ROWn; pin 1 is cathode at the per-key switch node.
J320 mirrors mainboard J310. Fit mainboard R387 for the RGB I2C buffer; keep R386 absent so the 5 V current limit cannot be bypassed.
Fit LEDs and support parts before the MX ULP switches. Follow CHERRY's assembly process and check a first article.
The split space layout is unchanged. Check the large keycaps and stabilizers with the actual switch/plate stack.
Legends/keycaps are mechanical deliverables: prototype blank resin/MJF caps and clip coupons before final legends or stabilizer bars.
keyboard rgb: 65 separate colours, hardware-limited current
Everlight 19-337/R6GHBHC-C02/2T, 1.6 x 1.6 x 0.35 mm; LEDs are fitted before the switches.
Physical rows use sink groups 1..5; the ten extra keys use group 6. Scan banks follow nearby columns.
J320 pin 29 is the switched 5 V rail. Pin 2 needs mainboard R387 fitted for the I2C buffer.
U321 A side is the main 3.3 V bus; B side is the switched 5 V RGB bus. Its power-off isolation keeps the unpowered LED driver off the EC bus.
ADDR1/ADDR2 at VCC select 7-bit address 0x2F. SDB rises through R323/C326; wait 20 ms before setup.
R320 limits peak sink current to about 11.3 mA at the datasheet corner: 18 active sinks stay below the cable budget.
Keep C322/C323 close to VCC, C324/C325 close to PVCC, and R320 close to ISET. Connect the exposed pad to ground.

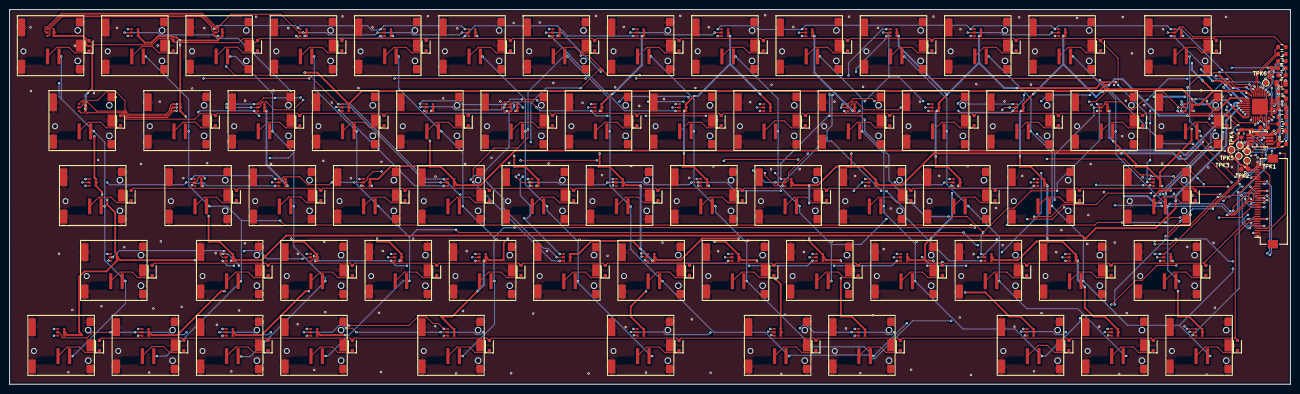
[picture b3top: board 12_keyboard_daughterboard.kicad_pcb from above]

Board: 4 copper layers, 273.5 x 80.0 mm, 221 parts (0 on the bottom side), 128 nets.

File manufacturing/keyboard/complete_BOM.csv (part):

Reference,Value,Manufacturer,MPN,LCSC,Footprint,Assembly
D320,1N4148WS,"Jiangsu Changjing Electronics Technology Co., Ltd.",1N4148WS,C2128,ducktop2:D_SOD-323_JSCJ_1N4148WS,factory
D321,1N4148WS,"Jiangsu Changjing Electronics Technology Co., Ltd.",1N4148WS,C2128,ducktop2:D_SOD-323_JSCJ_1N4148WS,factory
D322,1N4148WS,"Jiangsu Changjing Electronics Technology Co., Ltd.",1N4148WS,C2128,ducktop2:D_SOD-323_JSCJ_1N4148WS,factory
D323,1N4148WS,"Jiangsu Changjing Electronics Technology Co., Ltd.",1N4148WS,C2128,ducktop2:D_SOD-323_JSCJ_1N4148WS,factory
D324,1N4148WS,"Jiangsu Changjing Electronics Technology Co., Ltd.",1N4148WS,C2128,ducktop2:D_SOD-323_JSCJ_1N4148WS,factory
D325,1N4148WS,"Jiangsu Changjing Electronics Technology Co., Ltd.",1N4148WS,C2128,ducktop2:D_SOD-323_JSCJ_1N4148WS,factory
D326,1N4148WS,"Jiangsu Changjing Electronics Technology Co., Ltd.",1N4148WS,C2128,ducktop2:D_SOD-323_JSCJ_1N4148WS,factory
D327,1N4148WS,"Jiangsu Changjing Electronics Technology Co., Ltd.",1N4148WS,C2128,ducktop2:D_SOD-323_JSCJ_1N4148WS,factory
D328,1N4148WS,"Jiangsu Changjing Electronics Technology Co., Ltd.",1N4148WS,C2128,ducktop2:D_SOD-323_JSCJ_1N4148WS,factory
D329,1N4148WS,"Jiangsu Changjing Electronics Technology Co., Ltd.",1N4148WS,C2128,ducktop2:D_SOD-323_JSCJ_1N4148WS,factory
D330,1N4148WS,"Jiangsu Changjing Electronics Technology Co., Ltd.",1N4148WS,C2128,ducktop2:D_SOD-323_JSCJ_1N4148WS,factory
D331,1N4148WS,"Jiangsu Changjing Electronics Technology Co., Ltd.",1N4148WS,C2128,ducktop2:D_SOD-323_JSCJ_1N4148WS,factory
D332,1N4148WS,"Jiangsu Changjing Electronics Technology Co., Ltd.",1N4148WS,C2128,ducktop2:D_SOD-323_JSCJ_1N4148WS,factory
D333,1N4148WS,"Jiangsu Changjing Electronics Technology Co., Ltd.",1N4148WS,C2128,ducktop2:D_SOD-323_JSCJ_1N4148WS,factory
D334,1N4148WS,"Jiangsu Changjing Electronics Technology Co., Ltd.",1N4148WS,C2128,ducktop2:D_SOD-323_JSCJ_1N4148WS,factory
D335,1N4148WS,"Jiangsu Changjing Electronics Technology Co., Ltd.",1N4148WS,C2128,ducktop2:D_SOD-323_JSCJ_1N4148WS,factory
D336,1N4148WS,"Jiangsu Changjing Electronics Technology Co., Ltd.",1N4148WS,C2128,ducktop2:D_SOD-323_JSCJ_1N4148WS,factory
D337,1N4148WS,"Jiangsu Changjing Electronics Technology Co., Ltd.",1N4148WS,C2128,ducktop2:D_SOD-323_JSCJ_1N4148WS,factory
D338,1N4148WS,"Jiangsu Changjing Electronics Technology Co., Ltd.",1N4148WS,C2128,ducktop2:D_SOD-323_JSCJ_1N4148WS,factory
D339,1N4148WS,"Jiangsu Changjing Electronics Technology Co., Ltd.",1N4148WS,C2128,ducktop2:D_SOD-323_JSCJ_1N4148WS,factory
D340,1N4148WS,"Jiangsu Changjing Electronics Technology Co., Ltd.",1N4148WS,C2128,ducktop2:D_SOD-323_JSCJ_1N4148WS,factory
D341,1N4148WS,"Jiangsu Changjing Electronics Technology Co., Ltd.",1N4148WS,C2128,ducktop2:D_SOD-323_JSCJ_1N4148WS,factory
D342,1N4148WS,"Jiangsu Changjing Electronics Technology Co., Ltd.",1N4148WS,C2128,ducktop2:D_SOD-323_JSCJ_1N4148WS,factory
D343,1N4148WS,"Jiangsu Changjing Electronics Technology Co., Ltd.",1N4148WS,C2128,ducktop2:D_SOD-323_JSCJ_1N4148WS,factory
D344,1N4148WS,"Jiangsu Changjing Electronics Technology Co., Ltd.",1N4148WS,C2128,ducktop2:D_SOD-323_JSCJ_1N4148WS,factory
D345,1N4148WS,"Jiangsu Changjing Electronics Technology Co., Ltd.",1N4148WS,C2128,ducktop2:D_SOD-323_JSCJ_1N4148WS,factory
D346,1N4148WS,"Jiangsu Changjing Electronics Technology Co., Ltd.",1N4148WS,C2128,ducktop2:D_SOD-323_JSCJ_1N4148WS,factory
D347,1N4148WS,"Jiangsu Changjing Electronics Technology Co., Ltd.",1N4148WS,C2128,ducktop2:D_SOD-323_JSCJ_1N4148WS,factory
D348,1N4148WS,"Jiangsu Changjing Electronics Technology Co., Ltd.",1N4148WS,C2128,ducktop2:D_SOD-323_JSCJ_1N4148WS,factory
D349,1N4148WS,"Jiangsu Changjing Electronics Technology Co., Ltd.",1N4148WS,C2128,ducktop2:D_SOD-323_JSCJ_1N4148WS,factory
D350,1N4148WS,"Jiangsu Changjing Electronics Technology Co., Ltd.",1N4148WS,C2128,ducktop2:D_SOD-323_JSCJ_1N4148WS,factory
D351,1N4148WS,"Jiangsu Changjing Electronics Technology Co., Ltd.",1N4148WS,C2128,ducktop2:D_SOD-323_JSCJ_1N4148WS,factory
D352,1N4148WS,"Jiangsu Changjing Electronics Technology Co., Ltd.",1N4148WS,C2128,ducktop2:D_SOD-323_JSCJ_1N4148WS,factory
D353,1N4148WS,"Jiangsu Changjing Electronics Technology Co., Ltd.",1N4148WS,C2128,ducktop2:D_SOD-323_JSCJ_1N4148WS,factory
D354,1N4148WS,"Jiangsu Changjing Electronics Technology Co., Ltd.",1N4148WS,C2128,ducktop2:D_SOD-323_JSCJ_1N4148WS,factory
D355,1N4148WS,"Jiangsu Changjing Electronics Technology Co., Ltd.",1N4148WS,C2128,ducktop2:D_SOD-323_JSCJ_1N4148WS,factory
D356,1N4148WS,"Jiangsu Changjing Electronics Technology Co., Ltd.",1N4148WS,C2128,ducktop2:D_SOD-323_JSCJ_1N4148WS,factory
D357,1N4148WS,"Jiangsu Changjing Electronics Technology Co., Ltd.",1N4148WS,C2128,ducktop2:D_SOD-323_JSCJ_1N4148WS,factory
D358,1N4148WS,"Jiangsu Changjing Electronics Technology Co., Ltd.",1N4148WS,C2128,ducktop2:D_SOD-323_JSCJ_1N4148WS,factory
D359,1N4148WS,"Jiangsu Changjing Electronics Technology Co., Ltd.",1N4148WS,C2128,ducktop2:D_SOD-323_JSCJ_1N4148WS,factory
D360,1N4148WS,"Jiangsu Changjing Electronics Technology Co., Ltd.",1N4148WS,C2128,ducktop2:D_SOD-323_JSCJ_1N4148WS,factory
D361,1N4148WS,"Jiangsu Changjing Electronics Technology Co., Ltd.",1N4148WS,C2128,ducktop2:D_SOD-323_JSCJ_1N4148WS,factory
D362,1N4148WS,"Jiangsu Changjing Electronics Technology Co., Ltd.",1N4148WS,C2128,ducktop2:D_SOD-323_JSCJ_1N4148WS,factory
D363,1N4148WS,"Jiangsu Changjing Electronics Technology Co., Ltd.",1N4148WS,C2128,ducktop2:D_SOD-323_JSCJ_1N4148WS,factory
D364,1N4148WS,"Jiangsu Changjing Electronics Technology Co., Ltd.",1N4148WS,C2128,ducktop2:D_SOD-323_JSCJ_1N4148WS,factory
D365,1N4148WS,"Jiangsu Changjing Electronics Technology Co., Ltd.",1N4148WS,C2128,ducktop2:D_SOD-323_JSCJ_1N4148WS,factory
D366,1N4148WS,"Jiangsu Changjing Electronics Technology Co., Ltd.",1N4148WS,C2128,ducktop2:D_SOD-323_JSCJ_1N4148WS,factory
D367,1N4148WS,"Jiangsu Changjing Electronics Technology Co., Ltd.",1N4148WS,C2128,ducktop2:D_SOD-323_JSCJ_1N4148WS,factory
D368,1N4148WS,"Jiangsu Changjing Electronics Technology Co., Ltd.",1N4148WS,C2128,ducktop2:D_SOD-323_JSCJ_1N4148WS,factory
D369,1N4148WS,"Jiangsu Changjing Electronics Technology Co., Ltd.",1N4148WS,C2128,ducktop2:D_SOD-323_JSCJ_1N4148WS,factory
D370,1N4148WS,"Jiangsu Changjing Electronics Technology Co., Ltd.",1N4148WS,C2128,ducktop2:D_SOD-323_JSCJ_1N4148WS,factory
D371,1N4148WS,"Jiangsu Changjing Electronics Technology Co., Ltd.",1N4148WS,C2128,ducktop2:D_SOD-323_JSCJ_1N4148WS,factory
D372,1N4148WS,"Jiangsu Changjing Electronics Technology Co., Ltd.",1N4148WS,C2128,ducktop2:D_SOD-323_JSCJ_1N4148WS,factory
D373,1N4148WS,"Jiangsu Changjing Electronics Technology Co., Ltd.",1N4148WS,C2128,ducktop2:D_SOD-323_JSCJ_1N4148WS,factory
D374,1N4148WS,"Jiangsu Changjing Electronics Technology Co., Ltd.",1N4148WS,C2128,ducktop2:D_SOD-323_JSCJ_1N4148WS,factory
D375,1N4148WS,"Jiangsu Changjing Electronics Technology Co., Ltd.",1N4148WS,C2128,ducktop2:D_SOD-323_JSCJ_1N4148WS,factory
D376,1N4148WS,"Jiangsu Changjing Electronics Technology Co., Ltd.",1N4148WS,C2128,ducktop2:D_SOD-323_JSCJ_1N4148WS,factory
D377,1N4148WS,"Jiangsu Changjing Electronics Technology Co., Ltd.",1N4148WS,C2128,ducktop2:D_SOD-323_JSCJ_1N4148WS,factory
D378,1N4148WS,"Jiangsu Changjing Electronics Technology Co., Ltd.",1N4148WS,C2128,ducktop2:D_SOD-323_JSCJ_1N4148WS,factory
D379,1N4148WS,"Jiangsu Changjing Electronics Technology Co., Ltd.",1N4148WS,C2128,ducktop2:D_SOD-323_JSCJ_1N4148WS,factory
D380,1N4148WS,"Jiangsu Changjing Electronics Technology Co., Ltd.",1N4148WS,C2128,ducktop2:D_SOD-323_JSCJ_1N4148WS,factory
D381,1N4148WS,"Jiangsu Changjing Electronics Technology Co., Ltd.",1N4148WS,C2128,ducktop2:D_SOD-323_JSCJ_1N4148WS,factory
D382,1N4148WS,"Jiangsu Changjing Electronics Technology Co., Ltd.",1N4148WS,C2128,ducktop2:D_SOD-323_JSCJ_1N4148WS,factory
D383,1N4148WS,"Jiangsu Changjing Electronics Technology Co., Ltd.",1N4148WS,C2128,ducktop2:D_SOD-323_JSCJ_1N4148WS,factory
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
